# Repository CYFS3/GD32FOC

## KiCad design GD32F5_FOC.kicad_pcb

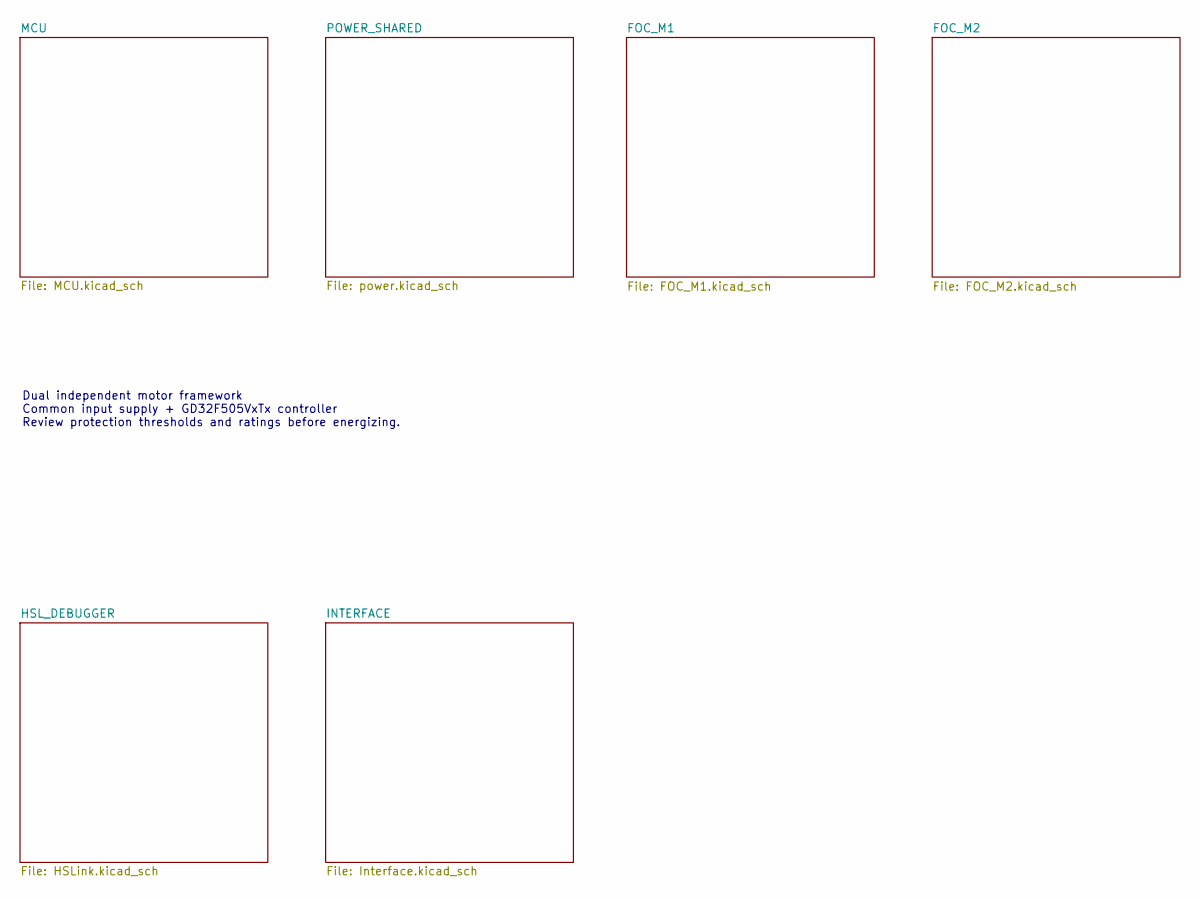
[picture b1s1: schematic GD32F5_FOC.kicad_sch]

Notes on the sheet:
Dual independent motor framework Common input supply + GD32F505VxTx controller Review protection thresholds and ratings before energizing.

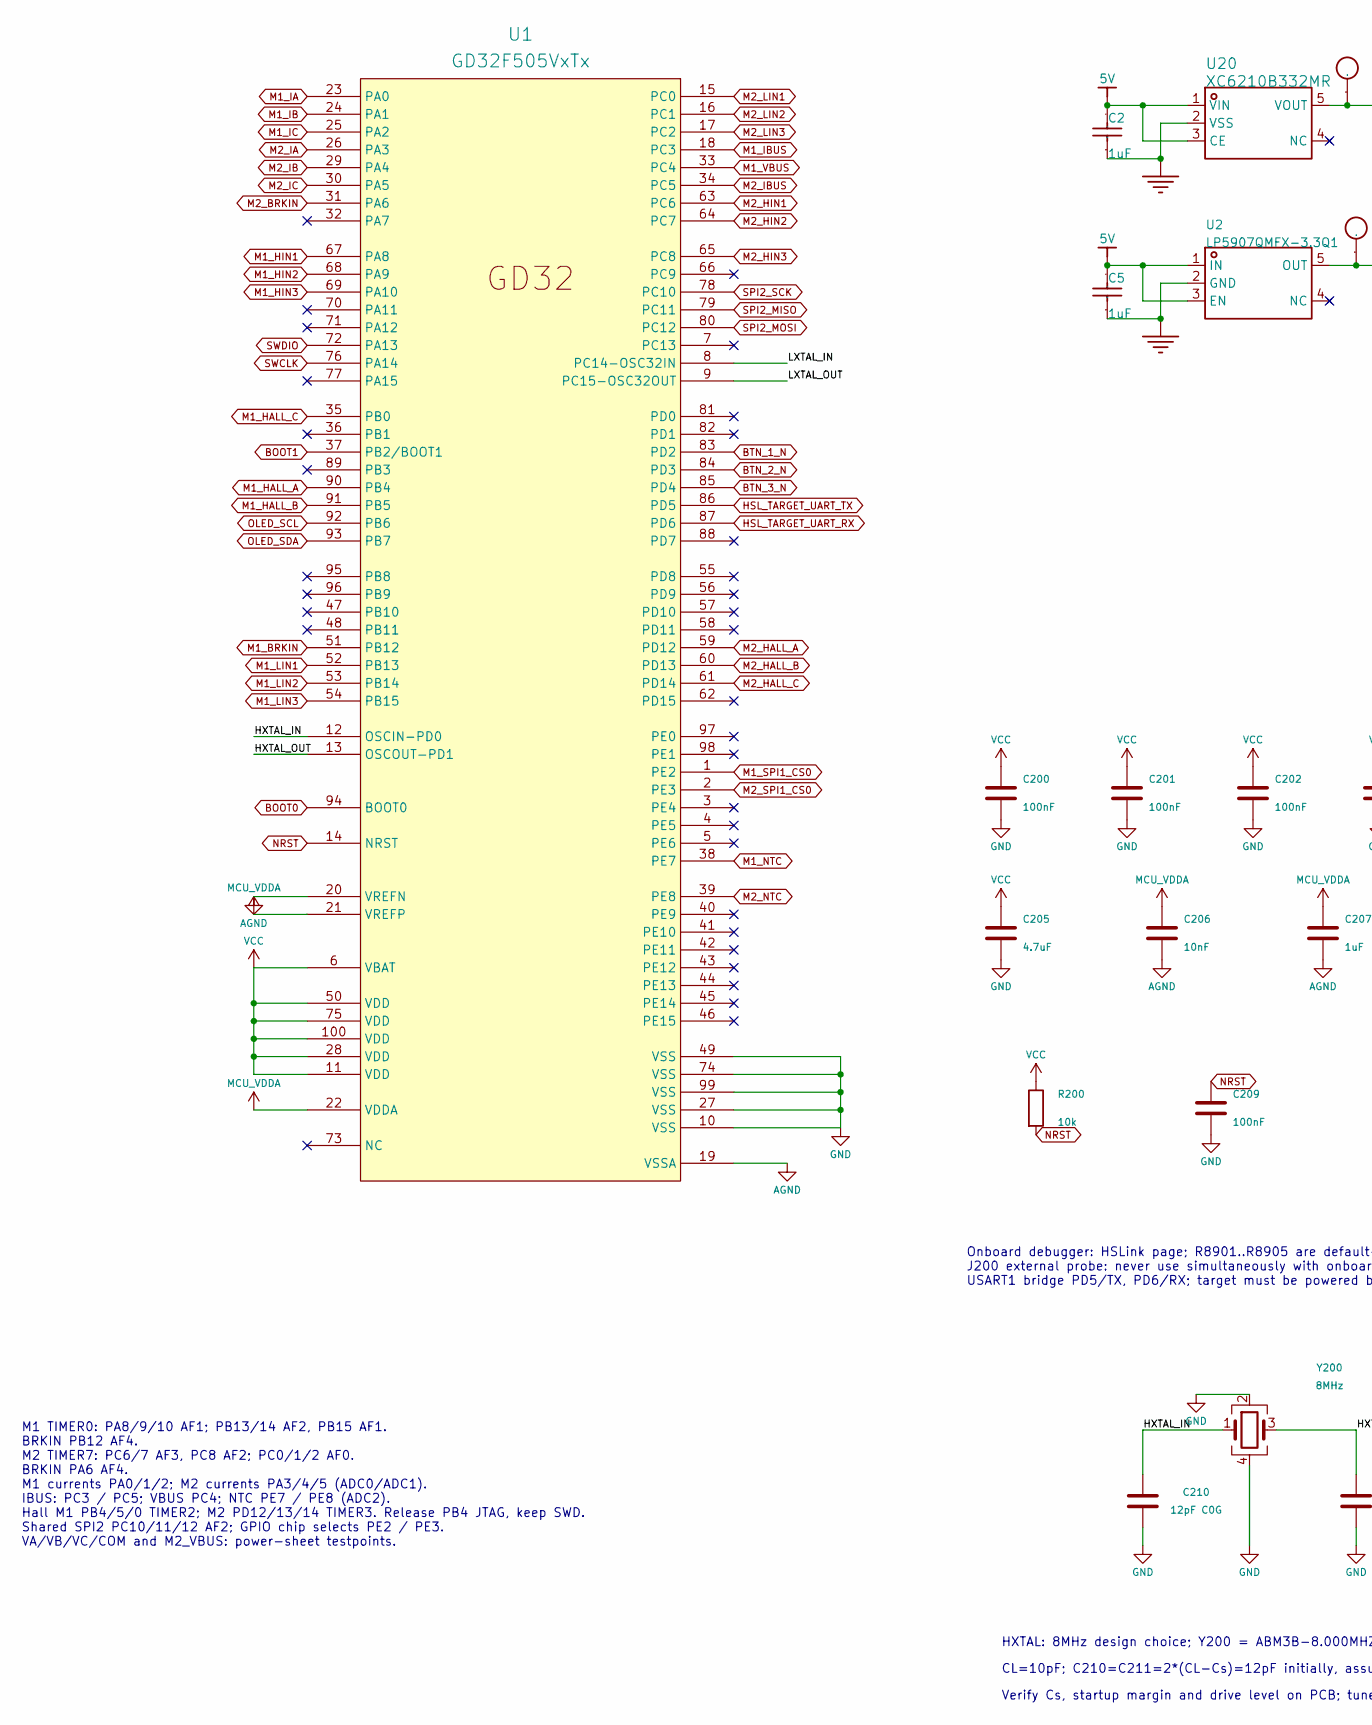
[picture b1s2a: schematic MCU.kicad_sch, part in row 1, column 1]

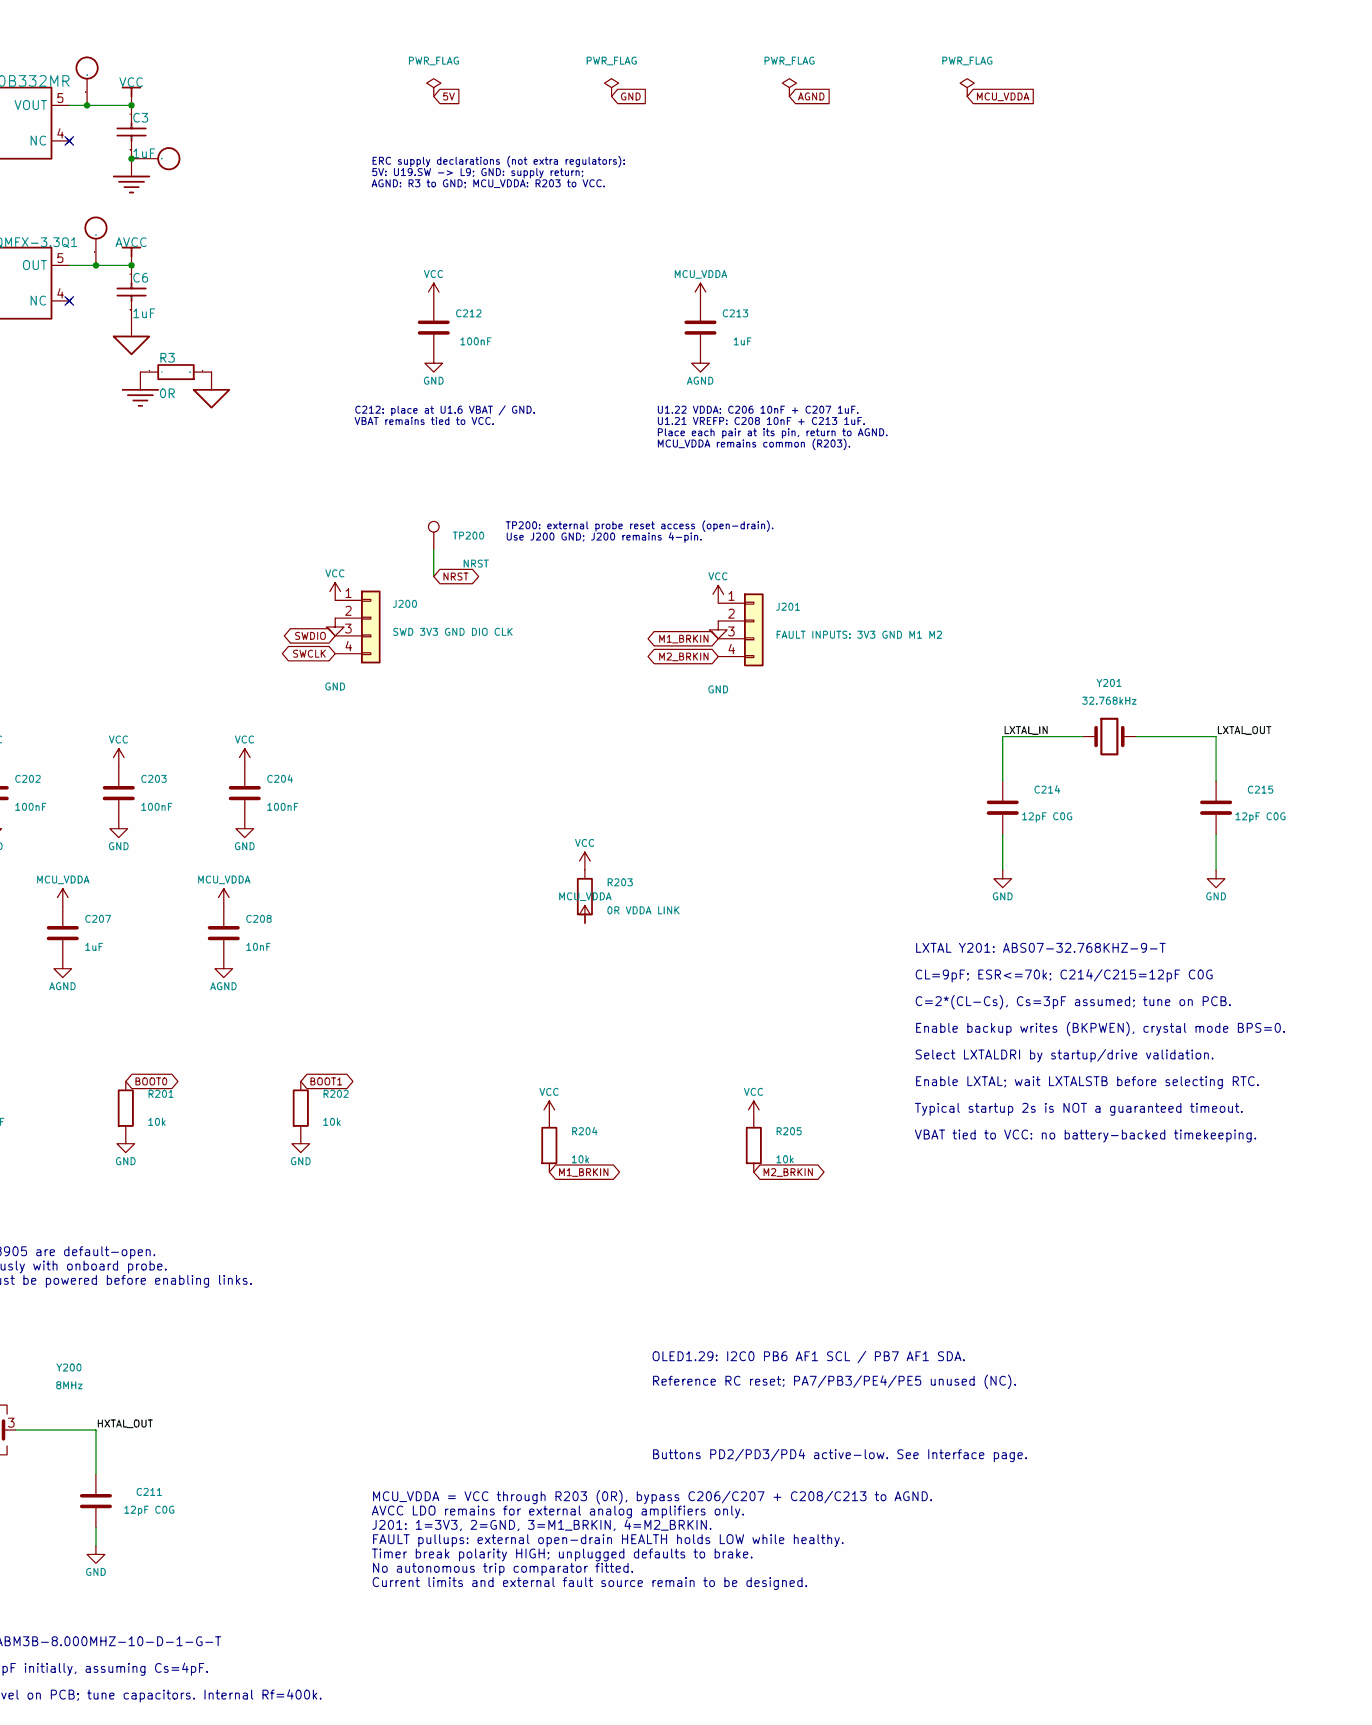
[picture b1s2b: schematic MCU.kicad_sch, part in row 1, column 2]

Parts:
C2, C3, C5, C6: 1uF; C0402; Tolerance ±10%; Voltage Rating 25V; Manufacturer Part CL05A105KA5NQNC; LCSC Part Name 1uF ±10% 25V
C200, C201, C202, C203, C204, C209, C212: 100nF; C_0603_1608Metric
C205: 4.7uF; C_0603_1608Metric
C206, C208: 10nF; C_0603_1608Metric
C207, C213: 1uF; C_0603_1608Metric
C210, C211, C214, C215: 12pF C0G; C_0603_1608Metric
CN2, CN3, CN6: TestPoint; TestPoint_D1.27_Reference; LCSC Part Name 测试点
J200: SWD 3V3 GND DIO CLK; PinHeader_1x04_P2.54mm_Vertical
J201: FAULT INPUTS: 3V3 GND M1 M2; PinHeader_1x04_P2.54mm_Vertical
R3: 0R; R0402; Manufacturer Part 0402WGF0000TCE
R200, R201, R202, R204, R205: 10k; R_0603_1608Metric
R203: 0R VDDA LINK; R_0603_1608Metric
TP200: NRST; TestPoint_Pad_D1.5mm
U1: GD32F505VxTx; LQFP100_14x14x1.6
U2: LP5907QMFX-3.3Q1; SOT-23-5_L3.0-W1.7-P0.95-LS2.8-BR; Manufacturer Part LP5907QMFX-3.3Q1; LCSC Part Name LP5907QMFX-3.3Q1
U20: XC6210B332MR; SOT-23-5_L3.0-W1.7-P0.95-LS2.8-BR; Manufacturer Part XC6210B332MR; LCSC Part Name XC6210B332MR
Y200: 8MHz; ABM3B_5x3.2mm; MPN ABM3B-8.000MHZ-10-D-1-G-T
Y201: 32.768kHz; ABS07_32.768kHz_3215; MPN ABS07-32.768KHZ-9-T

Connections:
5V: C2.2, C5.2, U2.1 (IN), U2.3 (EN), U20.1 (VIN), U20.3 (CE); also elsewhere on the board
/MCU/HXTAL_IN: C210.1, U1.12 (OSCIN-PD0), Y200.1
/MCU/HXTAL_OUT: C211.1, U1.13 (OSCOUT-PD1), Y200.3
/MCU/LXTAL_IN: C214.1, U1.8 (PC14-OSC32IN), Y201.1
/MCU/LXTAL_OUT: C215.1, U1.9 (PC15-OSC32OUT), Y201.2
AGND: C6.1, C206.2, C207.2, C208.2, C213.2, R3.1, U1.19 (VSSA), U1.20 (VREFN); also elsewhere on the board
AVCC: C6.2, CN6.1 (1_1), U2.5 (OUT); also elsewhere on the board
BOOT0: R201.1, U1.94 (BOOT0)
BOOT1: R202.1, U1.37 (PB2/BOOT1)
BTN_1_N: U1.83 (PD2); also elsewhere on the board
BTN_2_N: U1.84 (PD3); also elsewhere on the board
BTN_3_N: U1.85 (PD4); also elsewhere on the board
GND: C2.1, C3.1, C5.1, C200.2, C201.2, C202.2, C203.2, C204.2, C205.2, C209.2, C210.2, C211.2, C212.2, C214.2, C215.2, CN3.1 (1_1), J200.2, J201.2, R3.2, R201.2, R202.2, U1.10 (VSS), U1.27 (VSS), U1.49 (VSS), U1.74 (VSS), U1.99 (VSS), U2.2 (GND), U20.2 (VSS), Y200.2, Y200.4; also elsewhere on the board
HSL_TARGET_UART_RX: U1.87 (PD6); also elsewhere on the board
HSL_TARGET_UART_TX: U1.86 (PD5); also elsewhere on the board
M1_BRKIN: J201.3, R204.2, U1.51 (PB12)
M1_HALL_A: U1.90 (PB4); also elsewhere on the board
M1_HALL_B: U1.91 (PB5); also elsewhere on the board
M1_HALL_C: U1.35 (PB0); also elsewhere on the board
M1_HIN1: U1.67 (PA8); also elsewhere on the board
M1_HIN2: U1.68 (PA9); also elsewhere on the board
M1_HIN3: U1.69 (PA10); also elsewhere on the board
M1_IA: U1.23 (PA0); also elsewhere on the board
M1_IB: U1.24 (PA1); also elsewhere on the board
M1_IBUS: U1.18 (PC3); also elsewhere on the board
M1_IC: U1.25 (PA2); also elsewhere on the board
M1_LIN1: U1.52 (PB13); also elsewhere on the board
M1_LIN2: U1.53 (PB14); also elsewhere on the board
M1_LIN3: U1.54 (PB15); also elsewhere on the board
M1_NTC: U1.38 (PE7); also elsewhere on the board
M1_SPI1_CS0: U1.1 (PE2); also elsewhere on the board
M1_VBUS: U1.33 (PC4); also elsewhere on the board
M2_BRKIN: J201.4, R205.2, U1.31 (PA6)
M2_HALL_A: U1.59 (PD12); also elsewhere on the board
M2_HALL_B: U1.60 (PD13); also elsewhere on the board
M2_HALL_C: U1.61 (PD14); also elsewhere on the board
M2_HIN1: U1.63 (PC6); also elsewhere on the board
M2_HIN2: U1.64 (PC7); also elsewhere on the board
M2_HIN3: U1.65 (PC8); also elsewhere on the board
M2_IA: U1.26 (PA3); also elsewhere on the board
M2_IB: U1.29 (PA4); also elsewhere on the board
M2_IBUS: U1.34 (PC5); also elsewhere on the board
M2_IC: U1.30 (PA5); also elsewhere on the board
M2_LIN1: U1.15 (PC0); also elsewhere on the board
M2_LIN2: U1.16 (PC1); also elsewhere on the board
M2_LIN3: U1.17 (PC2); also elsewhere on the board
M2_NTC: U1.39 (PE8); also elsewhere on the board
M2_SPI1_CS0: U1.2 (PE3); also elsewhere on the board
MCU_VDDA: C206.1, C207.1, C208.1, C213.1, R203.2, U1.21 (VREFP), U1.22 (VDDA)
NRST: C209.1, R200.2, TP200.1 (1_1), U1.14 (NRST); also elsewhere on the board
OLED_SCL: U1.92 (PB6); also elsewhere on the board
OLED_SDA: U1.93 (PB7); also elsewhere on the board
SPI2_MISO: U1.79 (PC11); also elsewhere on the board
SPI2_MOSI: U1.80 (PC12); also elsewhere on the board
SPI2_SCK: U1.78 (PC10); also elsewhere on the board
SWCLK: J200.4, U1.76 (PA14); also elsewhere on the board
SWDIO: J200.3, U1.72 (PA13); also elsewhere on the board
VCC: C3.2, C200.1, C201.1, C202.1, C203.1, C204.1, C205.1, C212.1, CN2.1 (1_1), J200.1, J201.1, R200.1, R203.1, R204.1, R205.1, U1.6 (VBAT), U1.11 (VDD), U1.28 (VDD), U1.50 (VDD), U1.75 (VDD), U1.100 (VDD), U20.5 (VOUT); also elsewhere on the board

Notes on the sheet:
MCU_VDDA = VCC through R203 (0R), bypass C206/C207 + C208/C213 to AGND. AVCC LDO remains for external analog amplifiers only. J201: 1=3V3, 2=GND, 3=M1_BRKIN, 4=M2_BRKIN. FAULT pullups: external open-drain HEALTH holds LOW while healthy. Timer break polarity HIGH; unplugged defaults to brake. No aut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
M1 TIMER0: PA8/9/10 AF1; PB13/14 AF2, PB15 AF1. BRKIN PB12 AF4. M2 TIMER7: PC6/7 AF3, PC8 AF2; PC0/1/2 AF0. BRKIN PA6 AF4. M1 currents PA0/1/2; M2 currents PA3/4/5 (ADC0/ADC1). IBUS: PC3 / PC5; VBUS PC4; NTC PE7 / PE8 (ADC2). Hall M1 PB4/5/0 TIMER2; M2 PD12/13/14 TIMER3. Release PB4 JTAG, keep SWD.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
Onboard debugger: HSLink page; R8901..R8905 are default-open. J200 external probe: never use simultaneously with onboard probe. USART1 bridge PD5/TX, PD6/RX; target must be powered before enabling links.
Buttons PD2/PD3/PD4 active-low. See Interface page.
OLED1.29: I2C0 PB6 AF1 SCL / PB7 AF1 SDA.
Reference RC reset; PA7/PB3/PE4/PE5 unused (NC).
HXTAL: 8MHz design choice; Y200 = ABM3B-8.000MHZ-10-D-1-G-T
CL=10pF; C210=C211=2*(CL-Cs)=12pF initially, assuming Cs=4pF.
Verify Cs, startup margin and drive level on PCB; tune capacitors. Internal Rf=400k.
C212: place at U1.6 VBAT / GND. VBAT remains tied to VCC.
U1.22 VDDA: C206 10nF + C207 1uF. U1.21 VREFP: C208 10nF + C213 1uF. Place each pair at its pin, return to AGND. MCU_VDDA remains common (R203).
TP200: external probe reset access (open-drain). Use J200 GND; J200 remains 4-pin.
ERC supply declarations (not extra regulators): 5V: U19.SW -> L9; GND: supply return; AGND: R3 to GND; MCU_VDDA: R203 to VCC.
LXTAL Y201: ABS07-32.768KHZ-9-T
CL=9pF; ESR<=70k; C214/C215=12pF C0G
C=2*(CL-Cs), Cs=3pF assumed; tune on PCB.
Enable backup writes (BKPWEN), crystal mode BPS=0.
Select LXTALDRI by startup/drive validation.
Enable LXTAL; wait LXTALSTB before selecting RTC.
Typical startup 2s is NOT a guaranteed timeout.
VBAT tied to VCC: no battery-backed timekeeping.

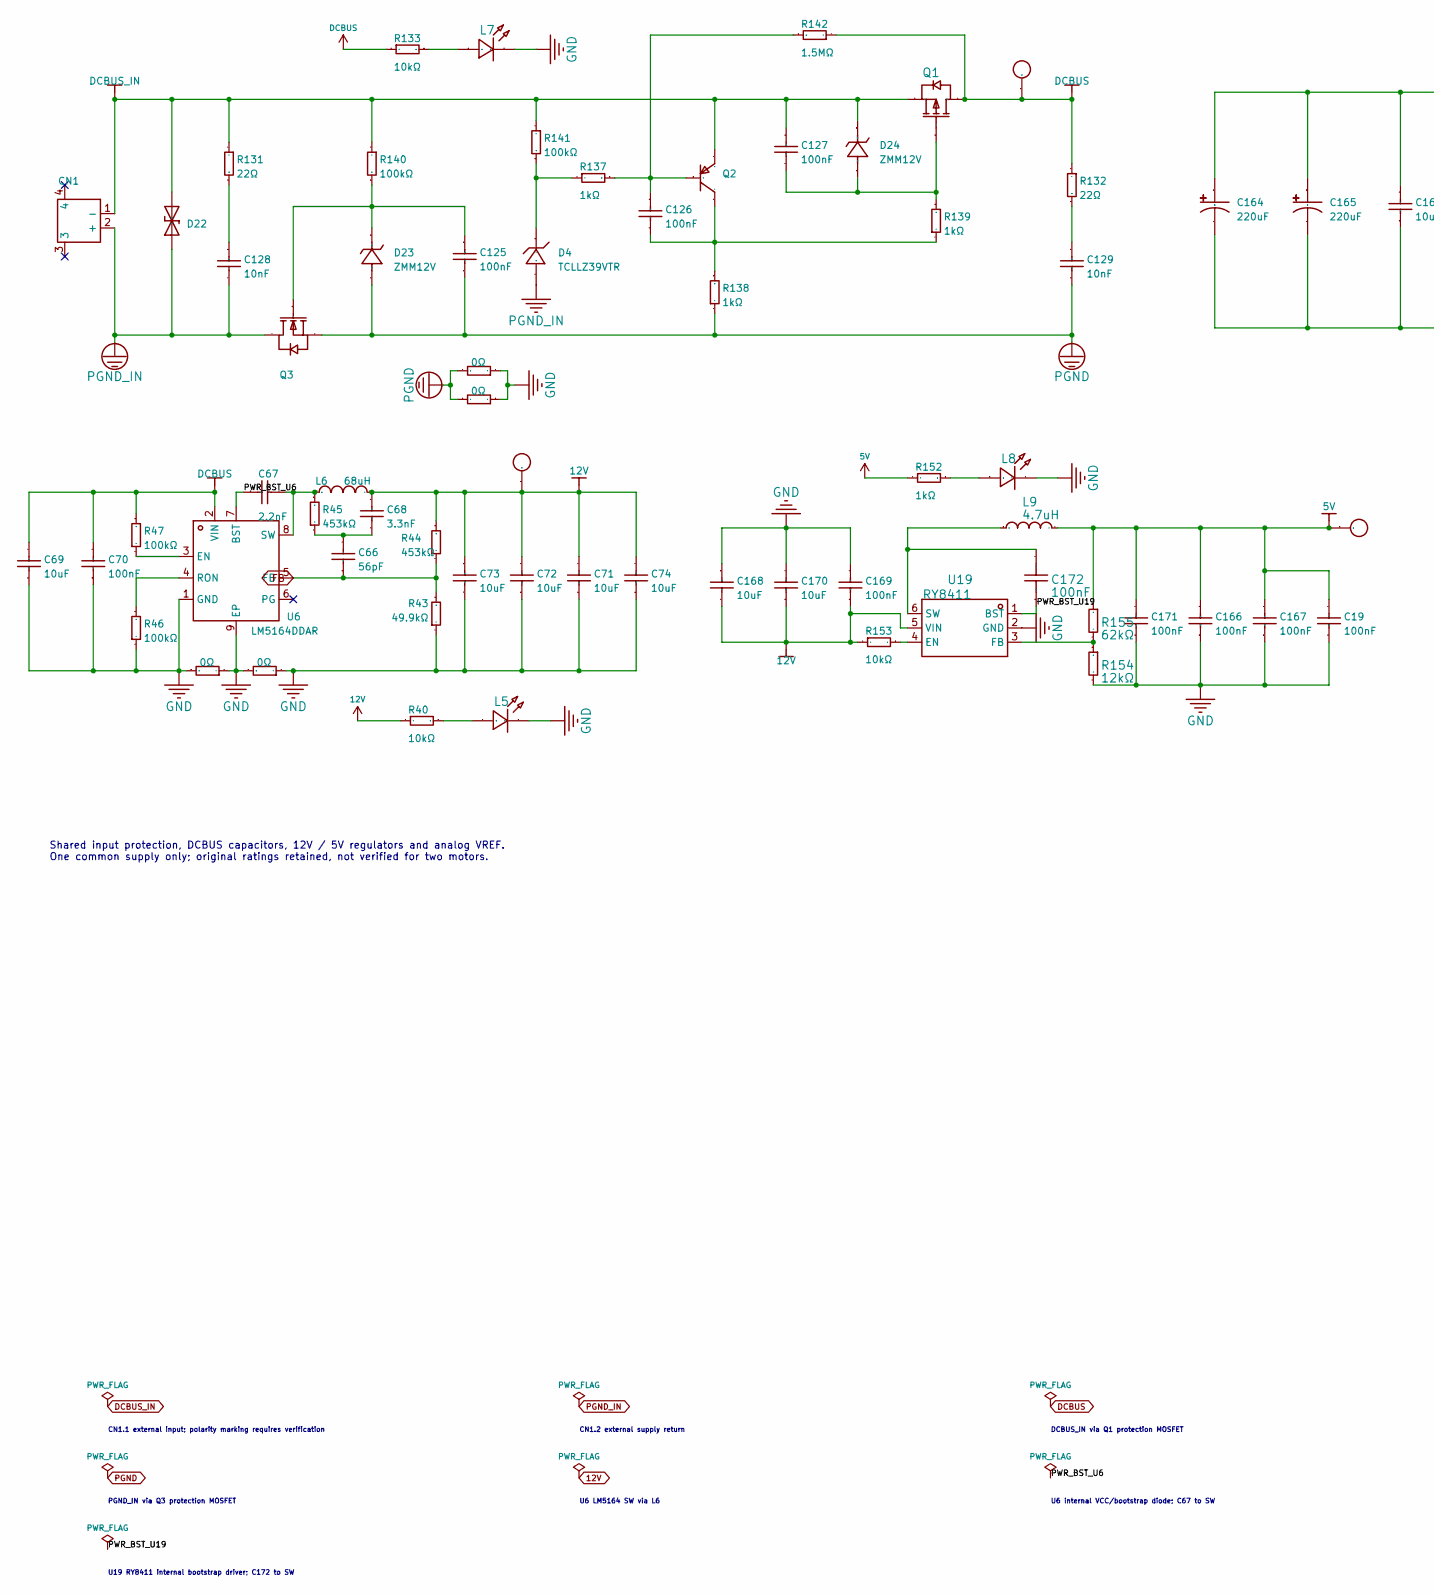
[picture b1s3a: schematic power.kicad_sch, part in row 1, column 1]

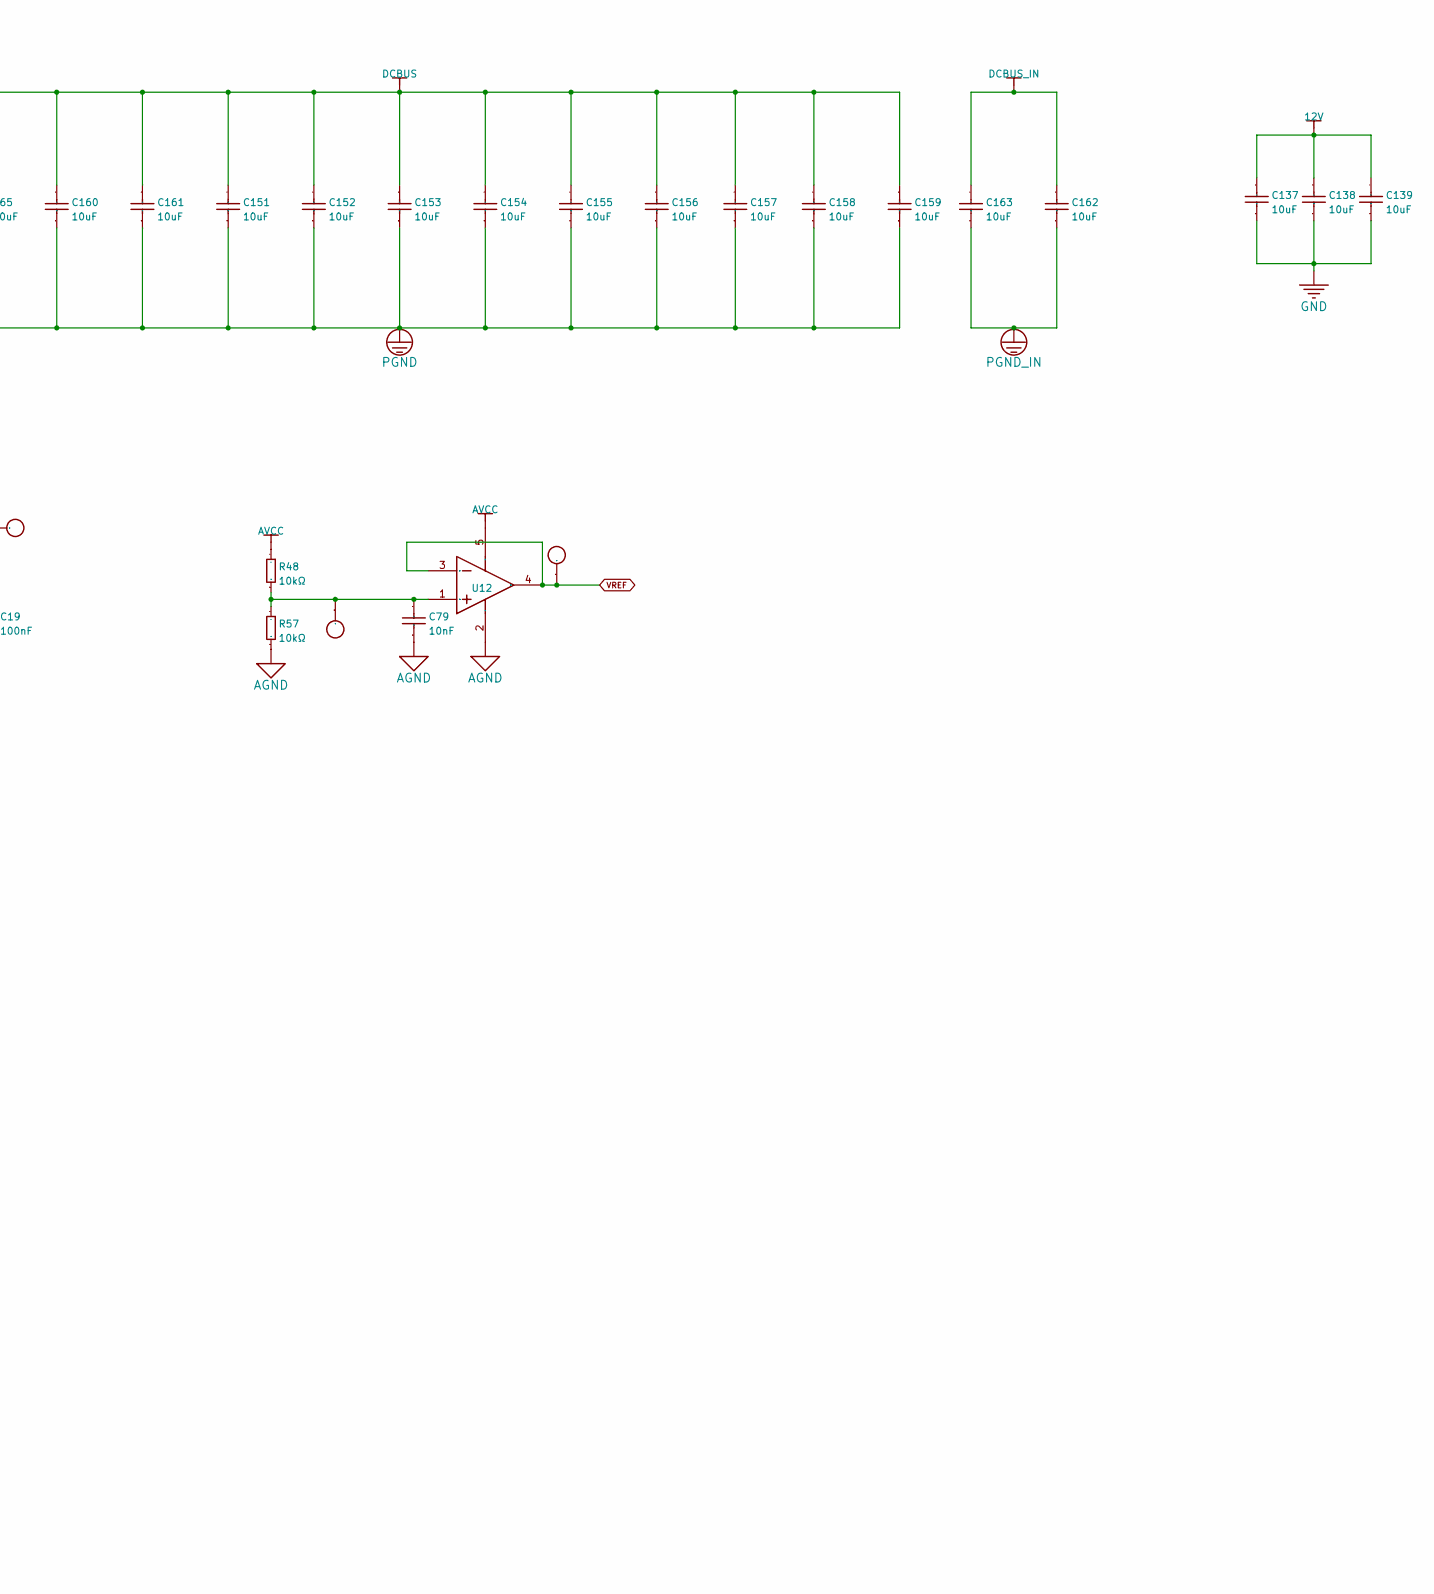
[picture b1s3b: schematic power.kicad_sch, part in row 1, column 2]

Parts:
C19, C125, C126, C127, C166, C167, C169, C171: 100nF; C0603_S; Tolerance ±10%; Voltage Rated 50V; Manufacturer Part 0603B104K500NT; LCSC Part Name 100nF ±10% 50V
C66: 56pF; C_0603_1608Metric; Tolerance ±5%; Voltage Rating 50V; Manufacturer Part 0603CG560J500NT; LCSC Part Name 56pF ±5% 50V
C67: 2.2nF; C_0603_1608Metric; Tolerance ±10%; Voltage Rating 50V; Manufacturer Part 0603B222K500NT; LCSC Part Name 2.2nF ±10% 50V
C68: 3.3nF; C_0603_1608Metric; Tolerance ±10%; Voltage Rated 50V; Manufacturer Part CL10B332KB8NNNC; LCSC Part Name 3.3nF ±10% 50V
C69: 10uF; C1206_S
C70: 100nF; C1206_S; Tolerance ±10%; Voltage Rated 50V; Manufacturer Part CL31B104KBCNNNC; LCSC Part Name 100nF ±10% 50V
C71, C72, C73, C137, C138, C139, C168, C170: 10uF; C0603_S; Tolerance ±20%; Voltage Rated 25V; Manufacturer Part CL10A106MA8NRNC; LCSC Part Name 10uF ±20% 25V
C74, C151, C152, C153, C154, C155, C156, C157, C158, C159, C160, C161, C162, C163: 10uF; C_1206_3216Metric; Tolerance ±10%; Voltage Rated 50V; Manufacturer Part CL31A106KBHNNNE; LCSC Part Name 10uF ±10% 50V
C79, C128, C129: 10nF; C0603_S; Tolerance ±10%; Voltage Rated 50V; Manufacturer Part 0603B103K500NT; LCSC Part Name 10nF ±10% 50V
C164, C165: 220uF; 50TZV220M10X10.5; Rated Voltage 50V; Tolerance ±20%; Manufacturer Part 50TZV220M10X10.5; LCSC Part Name 220uF ±20% 50V
C172: 100nF; C_0603_1608Metric; Tolerance ±10%; Voltage Rated 50V; Manufacturer Part CC0603KRX7R9BB104; LCSC Part Name 100nF ±10% 50V
CN1: XT30PW-M30.G.Y; CONN-TH_XT30PW-M; Manufacturer Part XT30PW-M30.G.Y; LCSC Part Name AMASS(艾迈斯)航模插头 卧式弯脚 XT30PW-M公头
CN4, CN7, CN9, CN13, CN16: TestPoint; TestPoint_D1.27_Reference; LCSC Part Name 测试点
D4: TCLLZ39VTR; D_MiniMELF; Tolerance ±5%; Zener Voltage (Nom) 39V; Manufacturer Part TCLLZ39VTR; LCSC Part Name TCLLZ39VTR
D22: 1.5SMC30CAHE3/57T; SMC_L6.8-W5.9-LS7.8-BI; Manufacturer Part 1.5SMC30CAHE3/57T; LCSC Part Name 1.5SMC30CAHE3/57T
D23, D24: ZMM12V; D_MiniMELF; Tolerance ±5%; Zener Voltage (Nom) 12V; Manufacturer Part ZMM12V; LCSC Part Name ZMM12V
L5, L7, L8: NCD0603R1; LED_0603_1608Metric_A1K2; Forward Voltage (VF) 1.6V~2.6V; Manufacturer Part NCD0603R1; LCSC Part Name 红灯 0603红灯 正贴
L6: 68uH; SMNR6045-680MT; Tolerance ±20%; Manufacturer Part SMNR6045-680MT; LCSC Part Name 68uH ±20% 1.2A
L9: 4.7uH; MPIH252010-4R7M-LF; Tolerance ±20%; Manufacturer Part MPIH252010-4R7M-LF; LCSC Part Name 4.7uH ±20% 1A 275mΩ
Q1: WSD90P06DN56; WSD90P06DN56_GDS123; Manufacturer Part WSD90P06DN56; LCSC Part Name P沟道 耐压:60V 电流:90A
Q2: FMMT593; SOT-23-3_L2.9-W1.3-P1.90-LS2.4-BR_1; Manufacturer Part FMMT593; LCSC Part Name FMMT593
Q3: WSD80120DN56; WSD80120DN56_GDS123; Manufacturer Part WSD80120DN56; LCSC Part Name WSD80120DN56
R40, R48, R57, R133, R153: 10kΩ; R0603_S; Overload Voltage (Max) 75V; Tolerance ±1%; Manufacturer Part 0603WAF1002T5E; LCSC Part Name 10kΩ ±1% 100mW 厚膜电阻
R41, R42, R134, R136: 0Ω; R0603_S; Overload Voltage (Max) 50V; Tolerance ±1%; Manufacturer Part RS-03000FT; LCSC Part Name 0Ω ±1% 100mW
R43: 49.9kΩ; R_0603_1608Metric; Overload Voltage (Max) 75V; Tolerance ±1%; Manufacturer Part 0603WAF4992T5E; LCSC Part Name 49.9kΩ ±1% 100mW 厚膜电阻
R44, R45: 453kΩ; R_0603_1608Metric; Overload Voltage (Max) 75V; Tolerance ±1%; Manufacturer Part 0603WAF4533T5E; LCSC Part Name 453kΩ ±1% 100mW 厚膜电阻
R46, R47: 100kΩ; R_0603_1608Metric; Overload Voltage (Max) 75V; Tolerance ±1%; Manufacturer Part RC0603FR-07100KL; LCSC Part Name 厚膜电阻 100kΩ ±1% 100mW
R131, R132: 22Ω; R0603_S; Overload Voltage (Max) 75V; Tolerance ±1%; Manufacturer Part 0603WAF220JT5E; LCSC Part Name 22Ω ±1% 100mW 厚膜电阻
R137, R138, R139, R152: 1kΩ; R0603_S; Overload Voltage (Max) 75V; Tolerance ±1%; Manufacturer Part RC0603FR-071KL; LCSC Part Name 1kΩ ±1% 100mW
R140, R141: 100kΩ; R0603_S; Overload Voltage (Max) 50V; Tolerance ±1%; Manufacturer Part RS-03K1003FT; LCSC Part Name 100kΩ ±1% 100mW
R142: 1.5MΩ; R0603_S; Overload Voltage (Max) 50V; Tolerance ±1%; Manufacturer Part RS-03L1504FT; LCSC Part Name 1.5MΩ ±1% 100mW
R154: 12kΩ; R_0603_1608Metric; Overload Voltage (Max) 75V; Tolerance ±1%; Manufacturer Part 0603WAF1202T5E; LCSC Part Name 12kΩ ±1% 100mW 厚膜电阻
R155: 62kΩ; R_0603_1608Metric; Overload Voltage (Max) 75V; Tolerance ±1%; Manufacturer Part 0603WAF6202T5E; LCSC Part Name 62kΩ ±1% 100mW 厚膜电阻
U6: LM5164DDAR; SO-8_L4.9-W3.9-P1.27-LS6.0-BL-EP; Input Voltage 6V~100V; Output Voltage 1.2V~100V; Manufacturer Part LM5164DDAR; LCSC Part Name 降压型 输入6V~100V 输出1.2V~100V 1A
U12: LM321MF/NOPB; SOT-23-5_L3.0-W1.7-P0.95-LS2.8-BR_1; Manufacturer Part LM321MF/NOPB; LCSC Part Name LM321MF/NOPB
U19: RY8411; SOT-23-6_L2.9-W1.6-P0.95-LS2.8-BR; Manufacturer Part JW5026; JLCPCB Part Class Extended Part

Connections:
5V: C19.2, C166.2, C167.2, C171.2, CN7.1 (1_1), L9.2, R152.2, R155.1; also elsewhere on the board
12V: C68.1, C71.2, C72.2, C73.1, C74.2, C137.2, C138.2, C139.2, C168.2, C169.1, C170.1, CN4.1 (1_1), L6.2, R40.2, R44.1, R153.2, U19.5 (VIN); also elsewhere on the board
/POWER_SHARED/PWR_BST_U6: C67.1, U6.7 (BST)
/POWER_SHARED/PWR_BST_U19: C172.1, U19.1 (BST)
AGND: C79.1, R57.1, U12.2 (V-); also elsewhere on the board
AVCC: R48.2, U12.5 (V+); also elsewhere on the board
DCBUS: C69.2, C70.2, C151.2, C152.2, C153.2, C154.2, C155.2, C156.2, C157.2, C158.2, C159.2, C160.2, C161.2, C164.1, C165.1, CN9.1 (1_1), Q1.2 (D), R47.1, R132.2, R133.2, R142.2, U6.2 (VIN); also elsewhere on the board
DCBUS_IN: C127.1, C162.2, C163.2, CN1.1 (-), D22.2 (A), D24.1 (K), Q1.3 (S), Q2.2 (E), R131.2, R140.2, R141.2
FB: C66.1, R43.1, R44.2, U6.5 (FB)
GND: C19.1, C69.1, C70.1, C71.1, C72.1, C73.2, C74.1, C137.1, C138.1, C139.1, C166.1, C167.1, C168.1, C169.2, C170.2, C171.1, L5.2, L7.2, L8.2, R41.1, R41.2, R42.1, R42.2, R43.2, R46.2, R134.2, R136.2, R154.2, U6.1 (GND), U6.9 (EP), U19.2 (GND); also elsewhere on the board
unnamed: C66.2, C68.2, R45.2
unnamed: C128.1, R131.1
unnamed: C129.1, R132.1
unnamed: D4.1 (C), R137.2, R141.1
unnamed: C125.1, D23.1 (K), Q3.1 (G), R140.1
unnamed: C127.2, D24.2 (A), Q1.1 (G), R139.1
unnamed: L5.1, R40.1
unnamed: L7.1, R133.1
unnamed: L8.1, R152.1
unnamed: C126.1, Q2.1 (B), R137.1, R142.1
unnamed: C126.2, Q2.3 (C), R138.1, R139.2
unnamed: R47.2, U6.3 (EN)
unnamed: R46.1, U6.4 (RON)
unnamed: C67.2, L6.1, R45.1, U6.8 (SW)
unnamed: C79.2, CN16.1 (1_1), R48.1, R57.2, U12.1 (IN+)
unnamed: R153.1, U19.4 (EN)
unnamed: R154.1, R155.2, U19.3 (FB)
unnamed: C172.2, L9.1, U19.6 (SW)
PGND: C125.2, C129.2, C151.1, C152.1, C153.1, C154.1, C155.1, C156.1, C157.1, C158.1, C159.1, C160.1, C161.1, C164.2, C165.2, D23.2 (A), Q3.3 (S), R134.1, R136.1, R138.2; also elsewhere on the board
PGND_IN: C128.2, C162.1, C163.1, CN1.2 (+), D4.2 (A), D22.1 (K), Q3.2 (D)
VREF: CN13.1 (1_1), U12.3 (IN-), U12.4 (OUT); also elsewhere on the board

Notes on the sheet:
Shared input protection, DCBUS capacitors, 12V / 5V regulators and analog VREF. One common supply only; original ratings retained, not verified for two motors.
CN1.1 external input; polarity marking requires verification
CN1.2 external supply return
DCBUS_IN via Q1 protection MOSFET
PGND_IN via Q3 protection MOSFET
U6 LM5164 SW via L6
U6 internal VCC/bootstrap diode; C67 to SW
U19 RY8411 internal bootstrap driver; C172 to SW
